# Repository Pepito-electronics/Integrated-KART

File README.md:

# Integrated-KART
Conception d'un KART électrique

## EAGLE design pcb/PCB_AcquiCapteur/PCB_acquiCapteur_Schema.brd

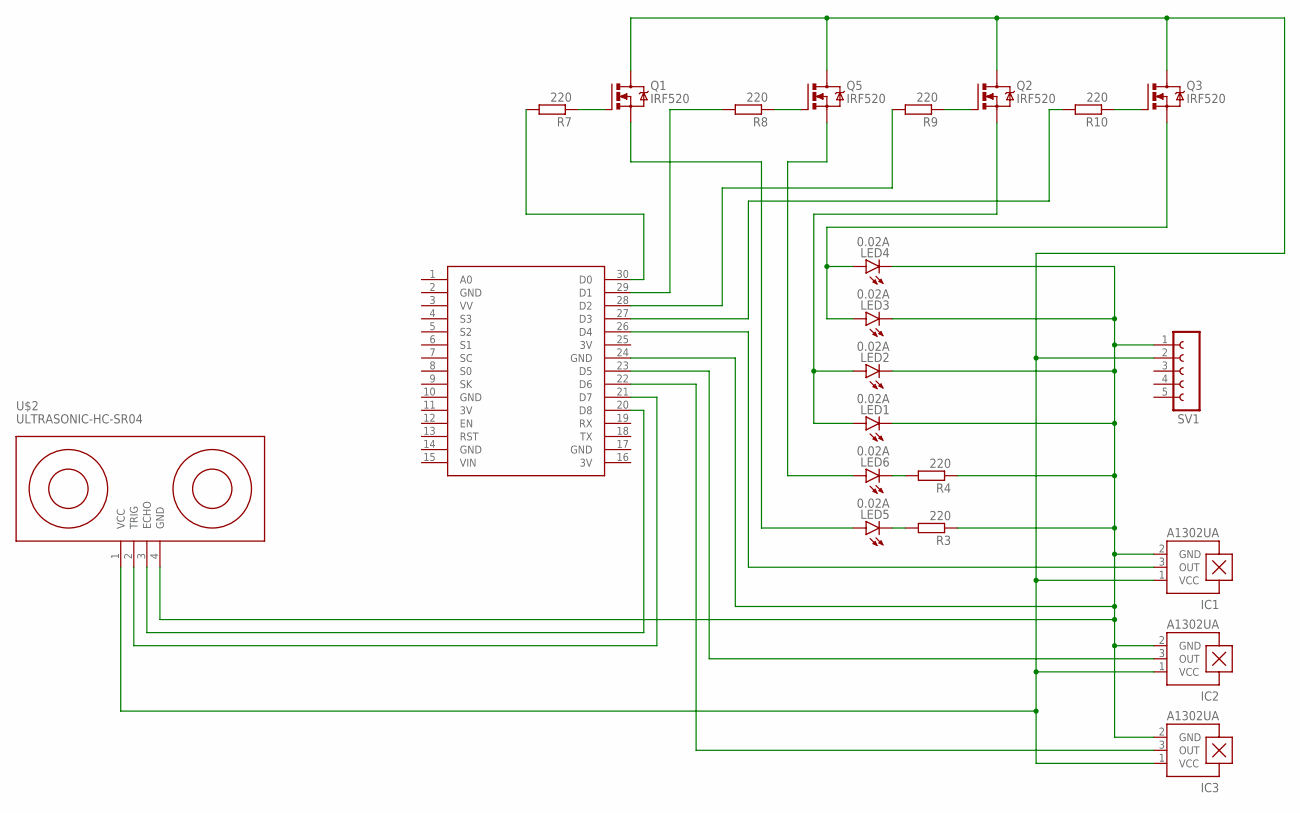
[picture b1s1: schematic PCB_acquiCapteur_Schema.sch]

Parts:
IC1, IC2, IC3: A1302UA; SIP3-UA
LED1, LED2, LED3, LED4, LED5, LED6: 0.02A; LSU260
Q1, Q2, Q3, Q5: IRF520; TO220BV
R3, R4, R7, R8, R9, R10: 220; 0207/10
SV1: FE05-1
U$1: NODEMCU
U$2: ULTRASONIC-HC-SR04

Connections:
3V: U$1.11 (3V), U$1.16 (3V), U$1.25 (3V)
GND: U$1.2 (GND), U$1.10 (GND), U$1.14 (GND), U$1.17 (GND)
unnamed: LED5.K (C), R3.2
unnamed: LED6.K (C), R4.2
unnamed: IC1.2 (GND), IC2.2 (GND), IC3.2 (GND), LED1.K (C), LED2.K (C), LED3.K (C), LED4.K (C), R3.1, R4.1, SV1.1, U$1.24 (GND), U$2.4 (GND)
unnamed: Q1.G, R7.1
unnamed: Q5.G, R8.1
unnamed: Q2.G, R9.1
unnamed: IC1.3 (OUT), U$1.26 (D4)
unnamed: IC2.3 (OUT), U$1.23 (D5)
unnamed: IC3.3 (OUT), U$1.22 (D6)
unnamed: IC1.1 (VCC), IC2.1 (VCC), IC3.1 (VCC), Q1.D, Q2.D, Q3.D, Q5.D, SV1.2, U$2.1 (VCC)
unnamed: U$1.20 (D8), U$2.3 (ECHO)
unnamed: U$1.21 (D7), U$2.2 (TRIG)
unnamed: Q3.G, R10.1
unnamed: R7.2, U$1.30 (D0)
unnamed: R8.2, U$1.29 (D1)
unnamed: R9.2, U$1.28 (D2)
unnamed: LED3.A, LED4.A, Q3.S
unnamed: LED1.A, LED2.A, Q2.S
unnamed: LED6.A, Q5.S
unnamed: LED5.A, Q1.S
unnamed: R10.2, U$1.27 (D3)

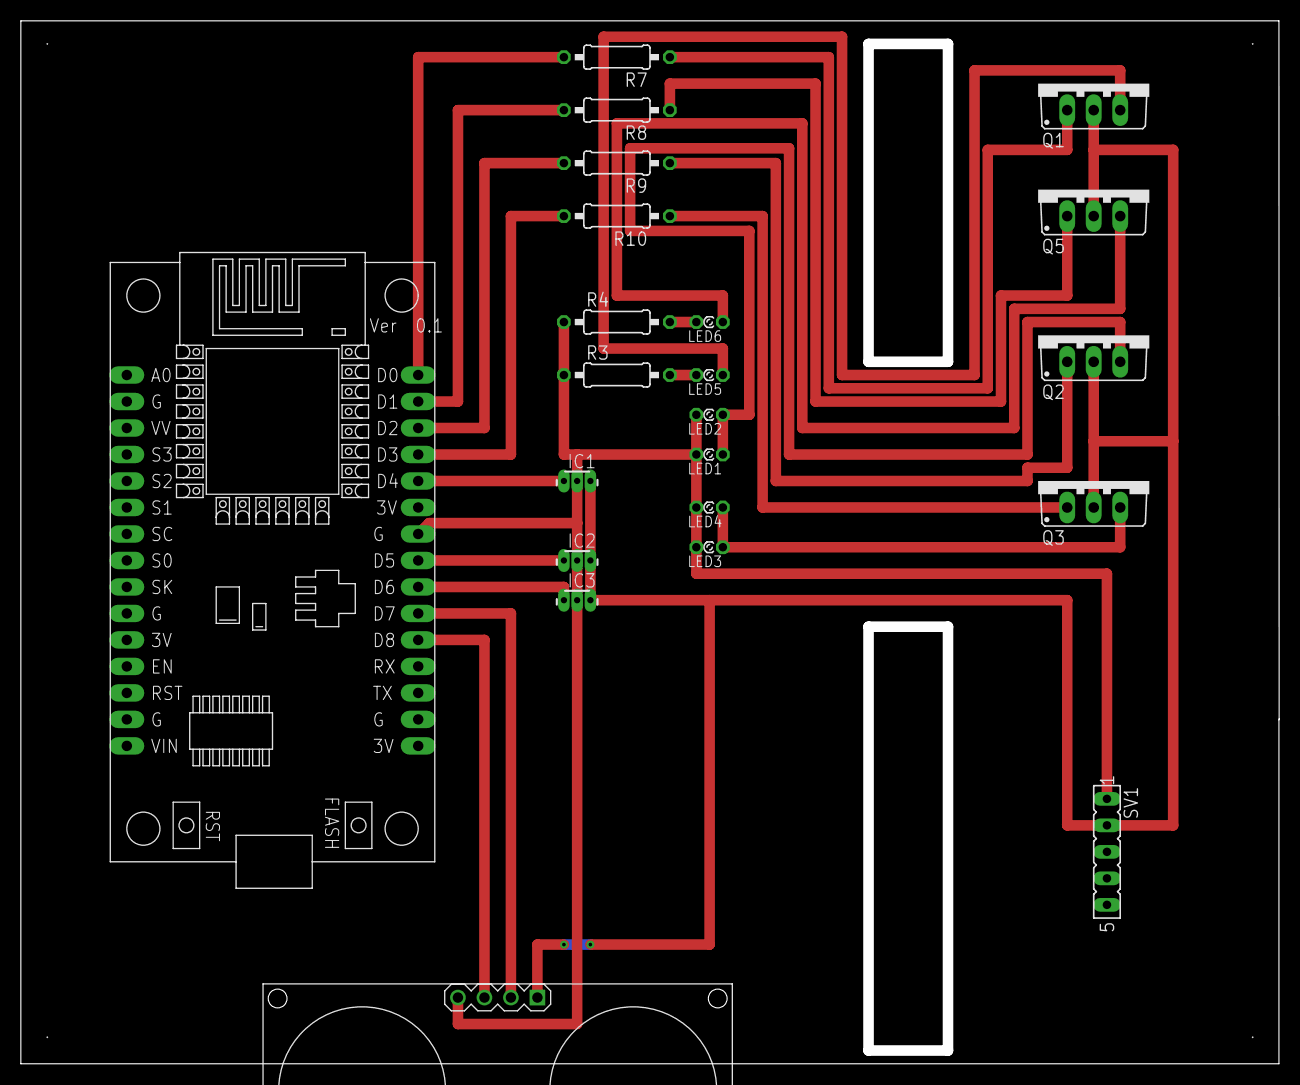
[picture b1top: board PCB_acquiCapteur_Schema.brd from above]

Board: 2 copper layers, 119.6 x 99.0 mm, 22 parts (0 on the bottom side), 23 nets.

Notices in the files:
parts and their libraries:
diy-modules: Released under the Creative Commons Attribution 4.0 International License: http://creativecommons.org/licenses/by/4.0
